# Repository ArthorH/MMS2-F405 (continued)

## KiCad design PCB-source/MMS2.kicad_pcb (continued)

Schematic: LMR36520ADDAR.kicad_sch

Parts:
C1, C2, C4, C5, C6, C7, C14, C15, C16: 10uF; C_0805; Voltage Rated 50V; Tolerance ±10%; Part GRM21BR61H106KE43L; LCSC C440198
C8, C9: 220nF; C_0805; Voltage Rated 50V; Tolerance ±10%; Part CL21B224KBFNNNE; LCSC C5378
C10: 100nF; C_0402; Voltage Rated 50V; Tolerance ±10%; Part CL05B104KB54PNC; LCSC C307331
C11, C12, C13, C22, C23, C24, C25, C28: 22uF; C_0805; Voltage Rated 25V; Tolerance ±20%; Part CL21A226MAQNNNE; LCSC C45783
C21, C27: 1uF; C_0402; Voltage Rated 25V; Tolerance ±10%; Part CL05A105KA5NQNC; LCSC C52923; not fitted
D1: SMF58CA; D_SOD-123FL; Clamping Voltage 93.6V; Voltage - Breakdown 71.2V; Part SMF58CA; LCSC C42371753
L1: CMPI0630-100M 10uH 4A; L_TechFuse_SL0620; LCSC C917354
R4, R8, R9: 24.9kΩ; R_0402; Overload Voltage (Max) 50V; Tolerance ±1%; Part 0402WGF2402TCE; LCSC C25874
R10: 10kΩ; R_0402; Overload Voltage (Max) 50V; Tolerance ±1%; Part 0402WGF1002TCE; LCSC C25744
R12: 100kΩ; R_0603; Overload Voltage (Max) 75V; Tolerance ±1%; Part 0603WAF1003T5E; LCSC C25803
U2: LMR36520ADDAR; Texas_HSOP-8-1EP_3.9x4.9mm_P1.27mm_ThermalVias; LCSC C2879422

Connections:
/VRM/LMR36520ADDAR/BOOT: C10.1, U2.7 (BOOT)
/VRM/LMR36520ADDAR/Cap_protec: C1.2, C2.1, C4.2, C5.1, C6.2, C7.1, C8.2, C9.1, C14.2, C15.1, D1.1, R8.2, R9.1
/VRM/LMR36520ADDAR/FB: R4.1, R12.2, U2.5 (FB)
/VRM/LMR36520ADDAR/LMR36520ADDAR_VOUT: C11.1, C12.1, C13.1, C21.1, C22.1, C23.1, C24.1, C25.1, C27.1, C28.1, L1.2, R12.1; also elsewhere on the board
/VRM/LMR36520ADDAR/PG: R10.1, U2.4 (PG)
/VRM/LMR36520ADDAR/SW: C10.2, L1.1, U2.8 (SW)
/VRM/LMR36520ADDAR/VCC: C16.1, R10.2, U2.6 (VCC)
BRD_VIN: C1.1, C4.1, C6.1, C8.1, C14.1, R8.1, U2.2 (VIN), U2.3 (EN); also elsewhere on the board
GND: C2.2, C5.2, C7.2, C9.2, C11.2, C12.2, C13.2, C15.2, C16.2, C21.2, C22.2, C23.2, C24.2, C25.2, C27.2, C28.2, D1.2, R4.2, R9.2, U2.1 (GND), U2.9 (GND); also elsewhere on the board

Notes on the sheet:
65V MAX
NO ALTERNATE PART AVALIABLE IF F-version is choosen instead of A-version it will have lower efficency at lower current due to F-ver being fixed freq
NOTE:
INFORMATION
KEEP CRIPPAGE DISTANCE 1.26MM MIN!
IEC 60664-1 Material Group III (CTI < 400; typical FR-4 = IIIa): 1.25 mm
Thats not sketch ... thats BOM-bastic!
saved for kebab on that one alone

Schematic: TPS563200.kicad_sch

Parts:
C17: 100nF; C_0402; Voltage Rated 50V; Tolerance ±10%; Part CL05B104KB54PNC; LCSC C307331
C18, C19, C20: 22uF; C_0805; Voltage Rated 25V; Tolerance ±20%; Part CL21A226MAQNNNE; LCSC C45783
D2: Red; D_0603; Part KT-0603R; LCSC C2286
JP301: SolderJumper_2_Bridged; SolderJumper-2_P1.3mm_Open_TrianglePad1.0x1.5mm
L301: 3.3uH; L_Changjiang_FXL0420; LCSC C167207
R11: 33.2kΩ; R_0402; Overload Voltage (Max) 50V; Tolerance ±1%; Part 0402WGF1002TCE; LCSC C122548
R13: 220Ω; R_0402; Overload Voltage (Max) 50V; Tolerance ±1%; Part 0402WGF2200TCE; LCSC C25091
R307: 10kΩ; R_0402; Overload Voltage (Max) 50V; Tolerance ±1%; Part 0402WGF1002TCE; LCSC C25744
U301: TPS563200; SOT-23-6; LCSC C116592

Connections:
+3V3: JP301.2 (B); also elsewhere on the board
+5V: C19.1, U301.3 (VIN), U301.5 (EN); also elsewhere on the board
/VRM/TPS563201/+3V3_UNPROTEC: C18.1, C20.1, D2.2, JP301.1 (A), L301.2, R11.1
/VRM/TPS563201/FB_3V3: R11.2, R307.1, U301.4 (VFB)
/VRM/TPS563201/SW_3V3: C17.1, L301.1, U301.2 (SW)
/VRM/TPS563201/VBST_3V3: C17.2, U301.6 (VBST)
GND: C18.2, C19.2, C20.2, R13.2, R307.2, U301.1 (GND); also elsewhere on the board
unnamed: D2.1, R13.1

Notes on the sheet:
CALCULATIONS:
NO ALTERNATE PART AVALIABLE Incompatible pinout. (tho at price of 0.2usd this is cheapest buck anyway)
NOTE:
V_{OUT} = 0.765*(1+33k2/10k) = 3.3V
V_{OUT} = 0.765*(1+R302/R307)

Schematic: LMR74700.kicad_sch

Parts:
C3: 100nF; C_0402; Voltage Rated 50V; Tolerance ±10%; Part CL05B104KB54PNC; LCSC C307331
Q7: AO3400A; Q_SOT-23; Part AO3400A; LCSC C20917
R7: 10kΩ; R_0402; Overload Voltage (Max) 50V; Tolerance ±1%; Part 0402WGF1002TCE; LCSC C25744
U5: LM74700; SOT-23-6; LCSC C2941042

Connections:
+5V: Q7.3 (D), U5.4 (CATHODE); also elsewhere on the board
/VRM/LMR36520ADDAR/LMR36520ADDAR_VOUT: C3.2, Q7.2 (S), R7.1, U5.6 (ANODE); also elsewhere on the board
GND: U5.2 (GND); also elsewhere on the board
unnamed: Q7.1 (G), U5.5 (GATE)
unnamed: R7.2, U5.3 (EN)
unnamed: C3.1, U5.1 (VCAP)

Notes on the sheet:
NOTE:
ALTERNATE PART: Wuxi Maxinmicro MX74700T PIN COMPATIBLE.

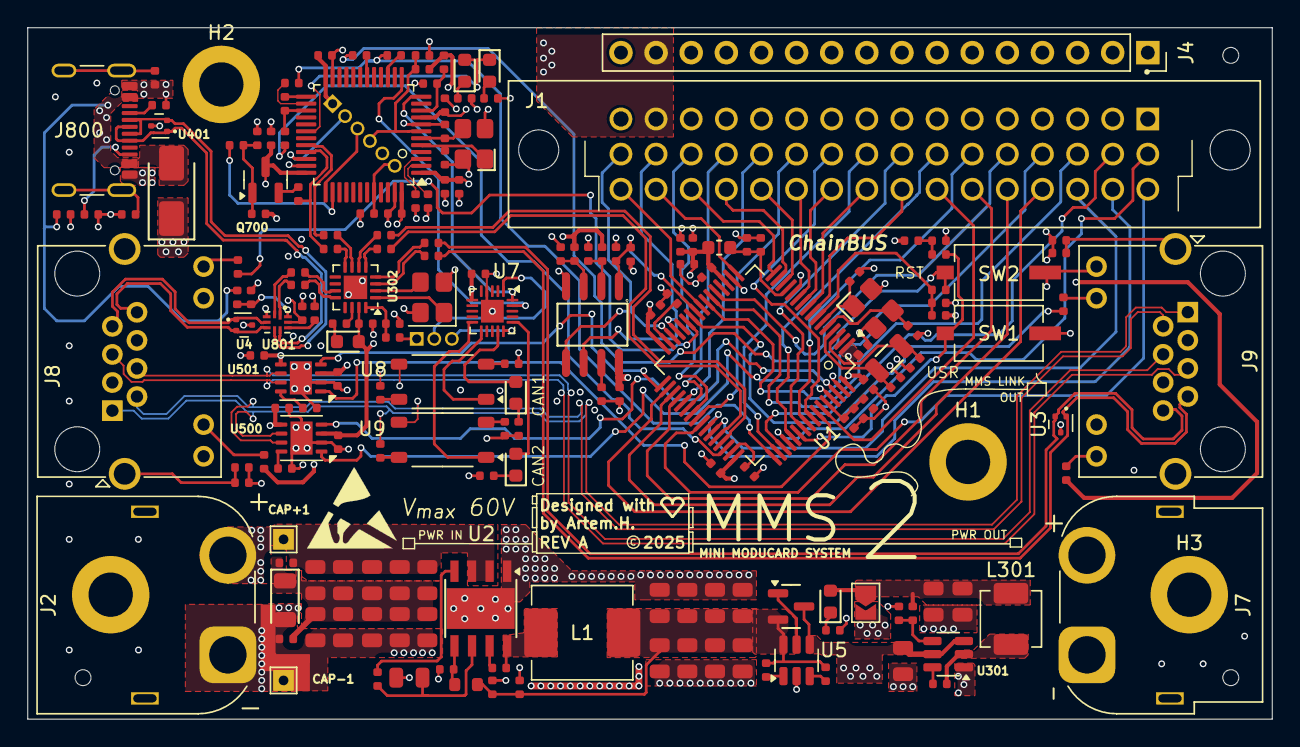
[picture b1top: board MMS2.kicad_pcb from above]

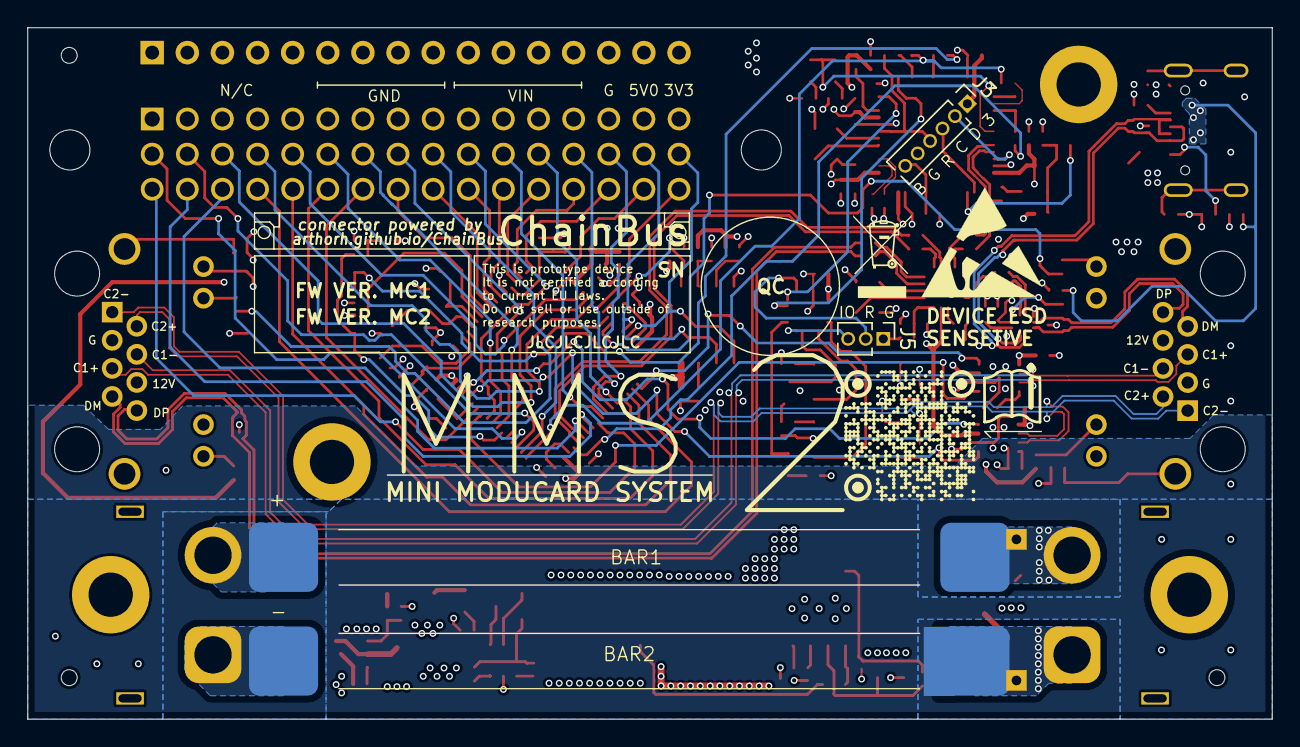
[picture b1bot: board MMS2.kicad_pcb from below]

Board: 4 copper layers, 90.0 x 50.0 mm, 192 parts (5 on the bottom side), 154 nets.

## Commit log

2025-09-15 F405 change compleate
2025-09-15 ch32
2025-09-18 Component placement done
2025-09-22 processor connection done
2025-09-22 add specification
2025-09-25 silk job, signal ratnest done
2025-09-26 change can term add usr led
2025-09-27 DRC PASS, preparing bom for production
2025-09-28 bom done
2025-09-29 REV A production ready
2025-09-29 Generate production files
